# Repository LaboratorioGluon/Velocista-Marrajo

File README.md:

# Velocista Marrajo

Robot velocista para competición.

## Componentes Principales

- ESC 4-en-1: https://s.click.aliexpress.com/e/_DDoQeDV
- Motores Ruedas (2004 1750KV): https://es.aliexpress.com/item/1005005199386587.html
- Motor Succion (GR1404 3850KV):  https://s.click.aliexpress.com/e/_DeUeUJD
- Procesador (ESP32): https://s.click.aliexpress.com/e/_DCxmJWF
- Sensores (ITR8307): https://s.click.aliexpress.com/e/_DEY47Gr
- Rodamientos (MR128 8x12x3.5, x4): https://s.click.aliexpress.com/e/_DeULPyP
- Engranaje (7T 1.48mm): https://s.click.aliexpress.com/e/_DDH1tE3
- Engranaje (423A, x2): https://s.click.aliexpress.com/e/_DeBl3bN

## Renders

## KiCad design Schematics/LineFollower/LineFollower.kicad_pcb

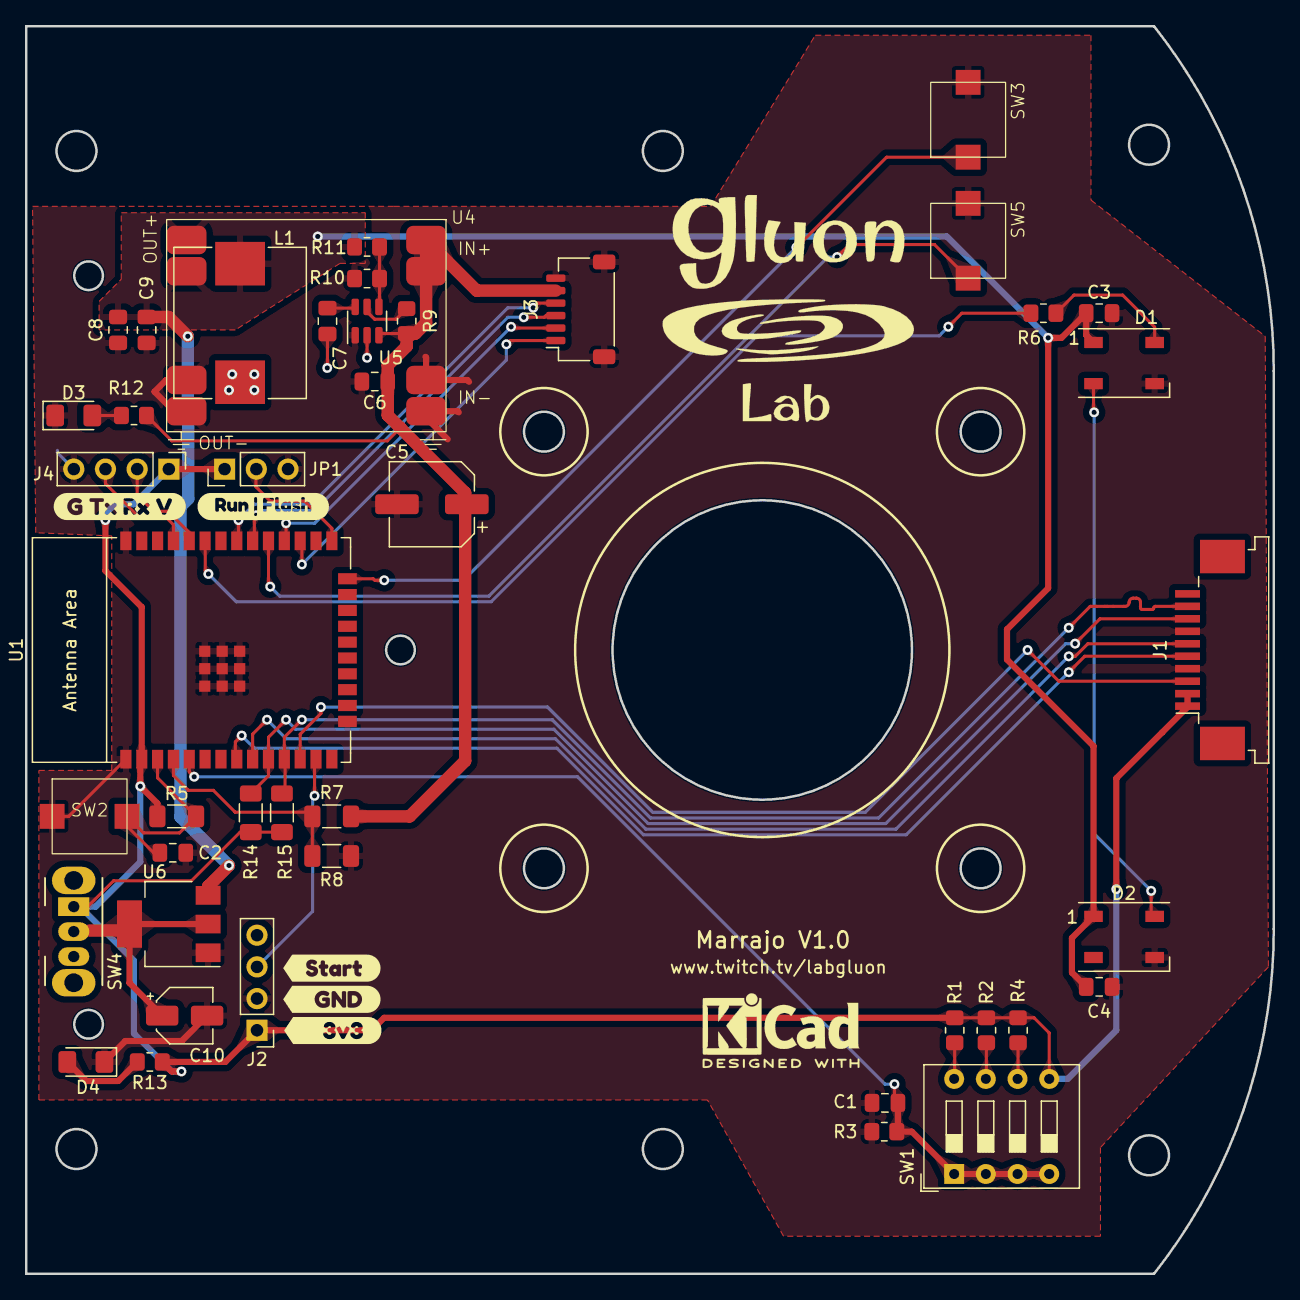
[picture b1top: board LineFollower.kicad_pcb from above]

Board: 2 copper layers, 100.0 x 100.0 mm, 49 parts (0 on the bottom side), 35 nets.

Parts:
C1, C2, C3, C4: 100nF; C_0805_2012Metric_Pad1.18x1.45mm_HandSolder
C5: 100u; CP_Elec_6.3x5.4
C6, C8, C9: 22u; C_0805_2012Metric_Pad1.18x1.45mm_HandSolder
C7: 100n; C_0805_2012Metric_Pad1.18x1.45mm_HandSolder
C10: C_Polarized_US; CP_Elec_4x5.3
D1, D2: WS2812B; LED_WS2812B_PLCC4_5.0x5.0mm_P3.2mm
D3: vBatt; LED_1206_3216Metric_Pad1.42x1.75mm_HandSolder
D4: 3v3; LED_1206_3216Metric_Pad1.42x1.75mm_HandSolder
J1: Morro; TE_1-84952-0_1x10-1MP_P1.0mm_Horizontal
J2: StartModule; PinHeader_1x04_P2.54mm_Vertical
J3: 4en1; JST_SH_SM06B-SRSS-TB_1x06-1MP_P1.00mm_Horizontal
J4: UART; PinHeader_1x04_P2.54mm_Vertical
JP1: BOOT_SELECT; PinHeader_1x03_P2.54mm_Vertical
L1: 3u3; L_Chilisin_BMRF00101040
R1, R12: 4k7; R_0805_2012Metric_Pad1.20x1.40mm_HandSolder
R2, R3: 2k2; R_0805_2012Metric_Pad1.20x1.40mm_HandSolder
R4, R13: 1k; R_0805_2012Metric_Pad1.20x1.40mm_HandSolder
R5, R8: 10k; R_1206_3216Metric_Pad1.30x1.75mm_HandSolder
R6: 470; R_0805_2012Metric_Pad1.20x1.40mm_HandSolder
R7: 47k; R_1206_3216Metric_Pad1.30x1.75mm_HandSolder
R9, R10: 10k; R_0805_2012Metric_Pad1.20x1.40mm_HandSolder
R11: 54k9; R_0805_2012Metric_Pad1.20x1.40mm_HandSolder
R14, R15: 2k; R_1206_3216Metric_Pad1.30x1.75mm_HandSolder
SW1: SW_DIP_x04; SW_DIP_SPSTx04_Slide_9.78x12.34mm_W7.62mm_P2.54mm
SW2: SW_Push; SKPMANE010 _Silicone_6x6mm
SW3: Push2; SKPMANE010 _Silicone_6x6mm
SW4: SW_Push_SPDT; SS12D07VG2
SW5: Start; SKPMANE010 _Silicone_6x6mm
U1: ESP32-WROOM-E; ESP32-WROOM-32E
U4: 5v-Reg
U5: TPS563201; SOT-23-6
U6: AMS1117-3.3; SOT-223-3_TabPin2
kibuzzard-65DCBE20: G***; kibuzzard-65DCBE20
kibuzzard-65DCBE24: G***; kibuzzard-65DCBE24
kibuzzard-65DCBE28: G***; kibuzzard-65DCBE28
kibuzzard-65DCBF71: G***; kibuzzard-65DCBF71
kibuzzard-65DCBFCA: G***; kibuzzard-65DCBFCA

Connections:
+3V3: J1.1, J1.2, J2.1, J4.1, JP1.1 (A), R1.2, R2.2, R4.2, R5.2, R13.1, R14.2, R15.2, SW1.5, SW4.1 (A), U1.2 (3V3)
+5V: C3.1, C4.1, C8.1, C9.1, D1.1 (VDD), D2.1 (VDD), L1.2, R11.2, U4.3 (Vout), U6.3 (VI)
/BOOT_SELECT: JP1.2 (C), U1.25 (GPIO0/BOOT/ADC2_CH1)
/CONFIG: C1.1, R3.2, SW1.1, SW1.2, SW1.3, SW1.4, U1.5 (SENSOR_VN/GPIO39/ADC1_CH3)
/MOSFET_PWM: J1.3, U1.12 (ADC2_CH7/GPIO27)
/MOTOR_1: J3.1, U1.27 (GPIO16)
/MOTOR_2: J3.2, U1.28 (GPIO17)
/MOTOR_3: J3.3, U1.30 (GPIO18)
/MOTOR_4: J3.4, U1.31 (GPIO19)
/Power/3v3: C10.1, SW4.2 (B), U6.2 (VO)
/RGB_PIN: R6.2, U1.33 (GPIO21)
/SCL: J1.8, R14.1, U1.10 (DAC_1/ADC2_CH8/GPIO25)
/SDA: J1.9, R15.1, U1.11 (DAC_2/ADC2_CH9/GPIO26)
/START: J2.3, U1.13 (MTMS/GPIO14/ADC2_CH6)
/UART_RX: J4.2, U1.34 (U0RXD/GPIO3)
/UART_TX: J4.3, U1.35 (U0TXD/GPIO1)
/V1: J1.5, U1.8 (32K_XP/GPIO32/ADC1_CH4)
/V2: J1.6, U1.9 (32K_XN/GPIO33/ADC1_CH5)
/V_BATT: C5.1, C6.1, J3.5, R7.1, R9.2, R12.1, U4.1 (Vin), U5.3 (VIN)
/V_BATT_SENSE: R7.2, R8.1, U1.4 (SENSOR_VP/GPIO36/ADC1_CH0)
GND: C1.2, C2.2, C3.2, C4.2, C5.2, C6.2, C8.2, C9.2, C10.2, D1.3 (VSS), D2.3 (VSS), D3.1 (K), D4.1 (K), J1.4, J1.7, J2.2, J3.6, J3.MP (MountPin), J4.4, JP1.3 (B), R3.1, R8.2, R10.2, SW2.1, SW3.2, SW5.2, U1.1 (GND), U1.15 (GND), U1.38 (GND), U1.39 (GND_THERMAL), U4.2 (Gnd), U4.4 (Gnd), U5.1 (GND), U6.1 (GND)
unnamed: D1.4 (DIN), R6.1
unnamed: D1.2 (DOUT), D2.4 (DIN)
unnamed: D3.2 (A), R12.2
unnamed: D4.2 (A), R13.2
unnamed: R1.1, SW1.8
unnamed: R2.1, SW1.7
unnamed: R4.1, SW1.6
unnamed: SW3.1, U1.24 (ADC2_CH2/GPIO2)
unnamed: C2.1, R5.1, SW2.2, U1.3 (EN/CHIP_PU)
unnamed: SW5.1, U1.29 (GPIO5)
unnamed: R9.1, U5.5 (EN)
unnamed: C7.2, L1.1, U5.2 (SW)
unnamed: C7.1, U5.6 (VBST)
unnamed: R10.1, R11.1, U5.4 (VFB)

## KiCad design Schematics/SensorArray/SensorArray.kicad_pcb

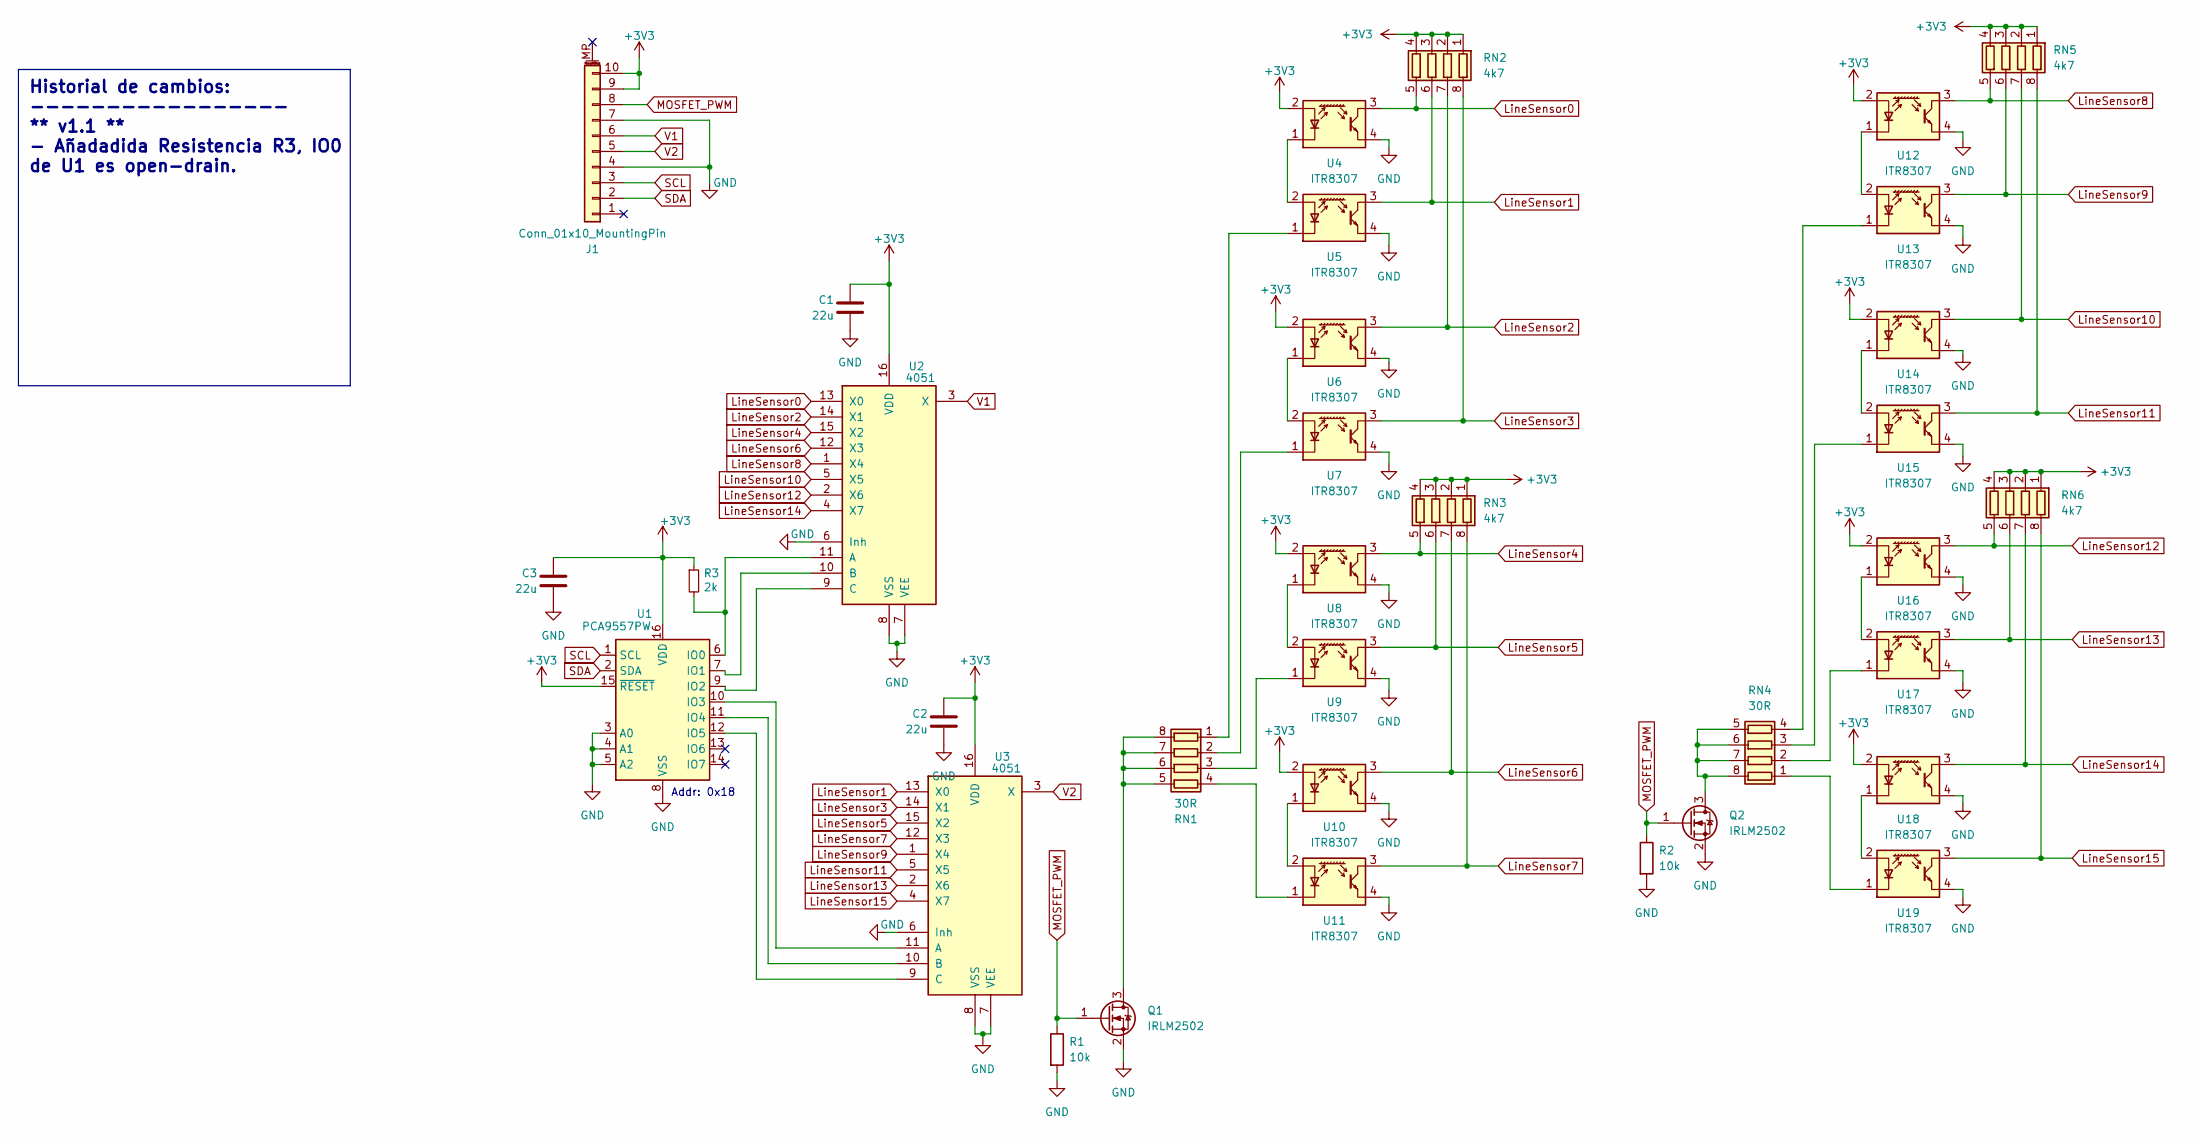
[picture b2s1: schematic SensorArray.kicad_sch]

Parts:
C1, C2, C3: 22u; C_0805_2012Metric_Pad1.18x1.45mm_HandSolder
J1: Conn_01x10_MountingPin; TE_1-84952-0_1x10-1MP_P1.0mm_Horizontal
Q1, Q2: IRLM2502; SOT-23
R1, R2: 10k; R_0805_2012Metric_Pad1.20x1.40mm_HandSolder
R3: 2k
RN1, RN4: 30R; R_Array_Convex_4x0603
RN2, RN3, RN5, RN6: 4k7; R_Array_Convex_4x0603
U1: PCA9557PW; TSSOP-16_4.4x5mm_P0.65mm
U2, U3: 4051; SOP-16_3.9x9.9mm_P1.27mm
U4, U5, U6, U7, U8, U9, U10, U11, U12, U13, U14, U15, U16, U17, U18, U19: ITR8307; Everlight_ITR1201SR10AR

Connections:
+3V3: C1.1, C2.1, C3.1, J1.9, J1.10, R3.1, RN2.1 (R1.1), RN2.2 (R2.1), RN2.3 (R3.1), RN2.4 (R4.1), RN3.1 (R1.1), RN3.2 (R2.1), RN3.3 (R3.1), RN3.4 (R4.1), RN5.1 (R1.1), RN5.2 (R2.1), RN5.3 (R3.1), RN5.4 (R4.1), RN6.1 (R1.1), RN6.2 (R2.1), RN6.3 (R3.1), RN6.4 (R4.1), U1.15 (~RESET), U1.16 (VDD), U2.16 (VDD), U3.16 (VDD), U4.2 (A), U6.2 (A), U8.2 (A), U10.2 (A), U12.2 (A), U14.2 (A), U16.2 (A), U18.2 (A)
GND: C1.2, C2.2, C3.2, J1.4, J1.7, Q1.2 (S), Q2.2 (S), R1.2, R2.2, U1.3 (A0), U1.4 (A1), U1.5 (A2), U1.8 (VSS), U2.6 (Inh), U2.7 (VEE), U2.8 (VSS), U3.6 (Inh), U3.7 (VEE), U3.8 (VSS), U4.4, U5.4, U6.4, U7.4, U8.4, U9.4, U10.4, U11.4, U12.4, U13.4, U14.4, U15.4, U16.4, U17.4, U18.4, U19.4
LineSensor0: RN2.5 (R4.2), U2.13 (X0), U4.3
LineSensor1: RN2.6 (R3.2), U3.13 (X0), U5.3
LineSensor2: RN2.7 (R2.2), U2.14 (X1), U6.3
LineSensor3: RN2.8 (R1.2), U3.14 (X1), U7.3
LineSensor4: RN3.5 (R4.2), U2.15 (X2), U8.3
LineSensor5: RN3.6 (R3.2), U3.15 (X2), U9.3
LineSensor6: RN3.7 (R2.2), U2.12 (X3), U10.3
LineSensor7: RN3.8 (R1.2), U3.12 (X3), U11.3
LineSensor8: RN5.5 (R4.2), U2.1 (X4), U12.3
LineSensor9: RN5.6 (R3.2), U3.1 (X4), U13.3
LineSensor10: RN5.7 (R2.2), U2.5 (X5), U14.3
LineSensor11: RN5.8 (R1.2), U3.5 (X5), U15.3
LineSensor12: RN6.5 (R4.2), U2.2 (X6), U16.3
LineSensor13: RN6.6 (R3.2), U3.2 (X6), U17.3
LineSensor14: RN6.7 (R2.2), U2.4 (X7), U18.3
LineSensor15: RN6.8 (R1.2), U3.4 (X7), U19.3
MOSFET_PWM: J1.8, Q1.1 (G), Q2.1 (G), R1.1, R2.1
unnamed: Q1.3 (D), RN1.5 (R4.2), RN1.6 (R3.2), RN1.7 (R2.2), RN1.8 (R1.2)
unnamed: Q2.3 (D), RN4.5 (R4.2), RN4.6 (R3.2), RN4.7 (R2.2), RN4.8 (R1.2)
unnamed: RN1.1 (R1.1), U5.1 (K)
unnamed: RN1.2 (R2.1), U7.1 (K)
unnamed: RN1.3 (R3.1), U9.1 (K)
unnamed: RN1.4 (R4.1), U11.1 (K)
unnamed: RN4.1 (R1.1), U19.1 (K)
unnamed: RN4.2 (R2.1), U17.1 (K)
unnamed: RN4.3 (R3.1), U15.1 (K)
unnamed: RN4.4 (R4.1), U13.1 (K)
unnamed: R3.2, U1.6 (IO0), U2.11 (A)
unnamed: U1.7 (IO1), U2.10 (B)
unnamed: U1.9 (IO2), U2.9 (C)
unnamed: U1.10 (IO3), U3.11 (A)
unnamed: U1.11 (IO4), U3.10 (B)
unnamed: U1.12 (IO5), U3.9 (C)
unnamed: U4.1 (K), U5.2 (A)
unnamed: U6.1 (K), U7.2 (A)
unnamed: U8.1 (K), U9.2 (A)
unnamed: U10.1 (K), U11.2 (A)
unnamed: U12.1 (K), U13.2 (A)
unnamed: U14.1 (K), U15.2 (A)
unnamed: U16.1 (K), U17.2 (A)
unnamed: U18.1 (K), U19.2 (A)
SCL: J1.3, U1.1 (SCL)
SDA: J1.2, U1.2 (SDA)
V1: J1.6, U2.3 (X)
V2: J1.5, U3.3 (X)

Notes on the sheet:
Historial de cambios: ----------------- ** v1.1 ** - Añadadida Resistencia R3, IO0 de U1 es open-drain.
Addr: 0x18

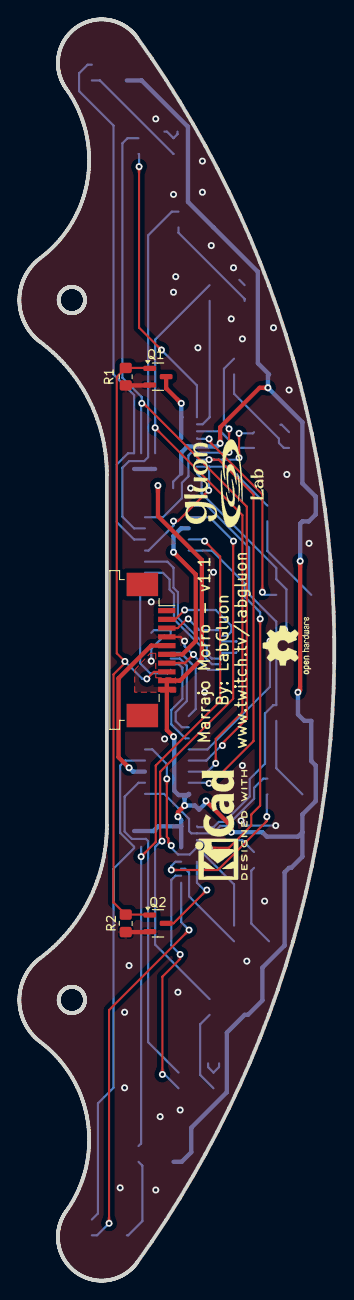
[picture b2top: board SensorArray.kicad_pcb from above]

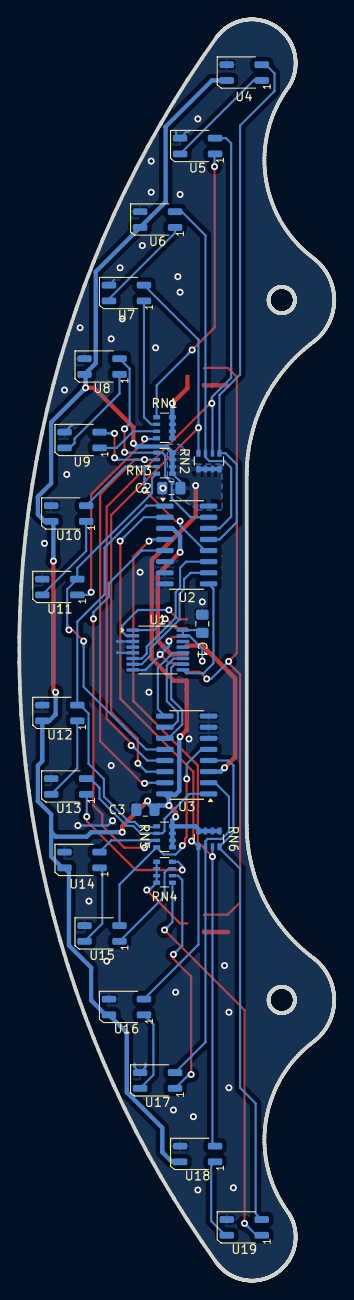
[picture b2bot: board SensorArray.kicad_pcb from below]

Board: 2 copper layers, 36.0 x 144.2 mm, 33 parts (28 on the bottom side), 47 nets.

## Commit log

2024-03-15 Uploaded V1.0 of PCB
2024-03-15 Deleted autosave file
2024-05-10 Version 1.1 PCB: Fixed I2C pullups
2024-05-10 SW: Calibration ready
2024-05-10 Config files
2024-06-21 Source: Added suction and BT control almost complete
